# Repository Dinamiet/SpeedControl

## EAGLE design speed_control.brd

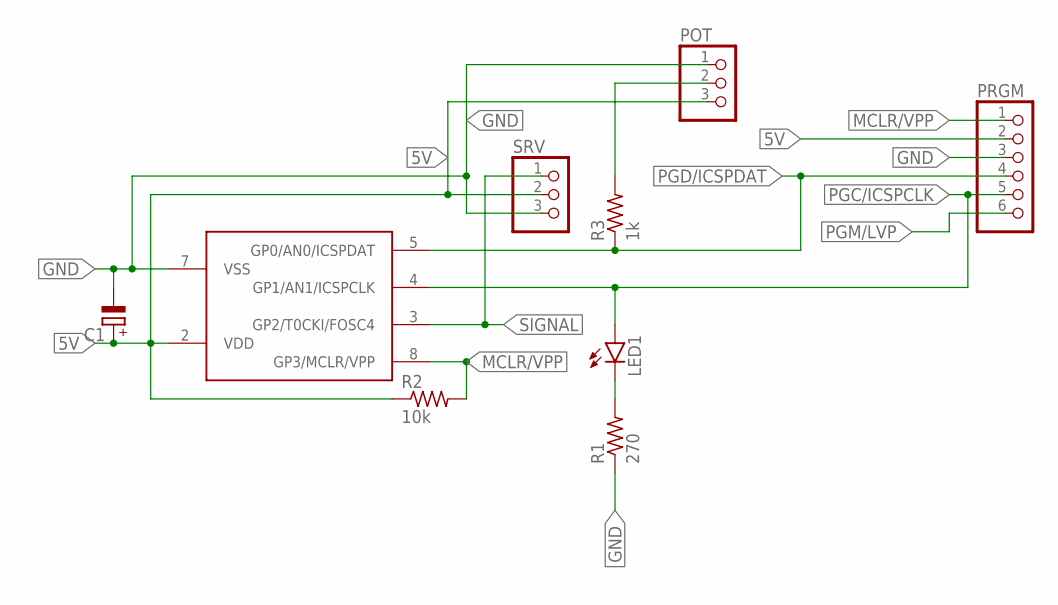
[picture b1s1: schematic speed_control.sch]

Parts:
C1: CPOL-EUE3.5-8; E3,5-8
LED1: LED3MM
POT: PINHD-1X3; 1X03
PRGM: PINHD-1X6; 1X06
R1: 270; 0207/10
R2: 10k; 0207/10
R3: 1k; 0207/10
SRV: PINHD-1X3/90; 1X03/90
U$1: PIC10F222PIC10F222; DIP762W53P254L955H330Q8B

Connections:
5V: C1.+, POT.3, PRGM.2, R2.1, SRV.2, U$1.2 (VDD)
GND: C1.-, POT.1, PRGM.3, R1.1, SRV.3, U$1.7 (VSS)
MCLR/VPP: PRGM.1, R2.2, U$1.8 (GP3/MCLR/VPP)
unnamed: POT.2, R3.2
unnamed: LED1.K (C), R1.2
PGC/ICSPCLK: LED1.A, PRGM.5, U$1.4 (GP1/AN1/ICSPCLK)
PGD/ICSPDAT: PRGM.4, R3.1, U$1.5 (GP0/AN0/ICSPDAT)
PGM/LVP: PRGM.6
SIGNAL: SRV.1, U$1.3 (GP2/T0CKI/FOSC4)

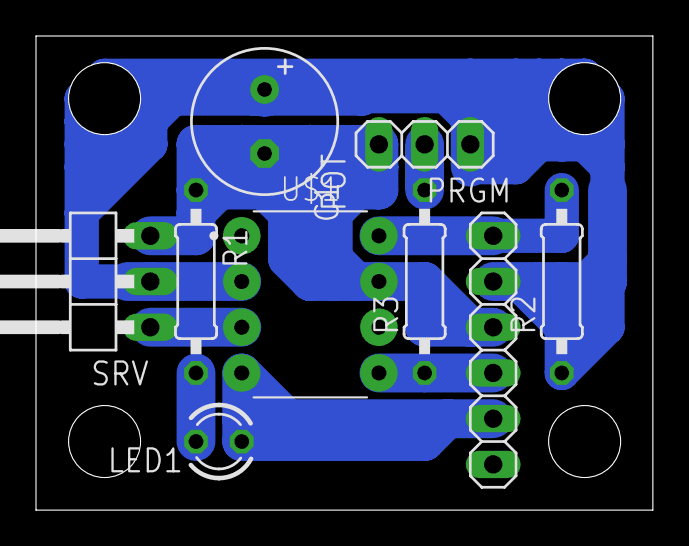
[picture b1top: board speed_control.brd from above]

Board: 2 copper layers, 34.3 x 26.3 mm, 9 parts (0 on the bottom side), 8 nets.

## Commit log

2020-01-28 Added headers to circuit
2020-01-29 Added programming interface
2020-02-01 Layout of PCB complete
2020-02-01 Moved board to origin
2020-02-01 Added mplab project
2020-02-01 New working project
2020-02-01 Almost there with code
2020-02-02 Servo timing sorted
2020-02-02 Servo moving with pod value
2020-02-02 Improved signal pulse
2020-02-02 Added code formatter
2020-02-02 Ran though formatter
2020-02-02 Servo movement sorted, LED not being used
2020-02-02 Watchdog caused reset
2020-02-02 Flasing LED
2020-02-02 Project updates
2020-02-02 Added CAP to circuit
2020-02-08 Added mounting holes
